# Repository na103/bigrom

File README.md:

# A590 Bigrom
Bigrom is an adapter that allows you to use a larger 256kbit ROM with the Commodore A590.<br>
It's useful for testing other firmwares that require more space and don't fit within the 128kbit limit imposed by the board's pinout.<br>
The ATF16V8C logic automatically asserts the A14 pin after reading the first 128kbit bank, allowing you to read the entire ROM content.
<br><br>

## Bill of materials
| Qt. |    Description     |             Designator          |    Mouser Part     |             Note              |
|:---:|--------------------|---------------------------------|--------------------|-------------------------------|
|1    |EEPROM 256K         |U2                               |AT28HC256F-90SU     |   need programmer like TL866  |
|1    |EEPLD               |U1                               |ATF16V8CZ-15SU      |   need programmer like TL866  |
|2    |Header Strip        |J1                               |D01-9923246         |                               |

## Building notes
The EEPROM can be soldered onto the PCB but it must be programmed before soldering the GAL (SW1 and SW3 closed).<br>
Programming of the ATF16V8 must be done before soldering using the TL866 with a SOIC socket adapter.<br>
in working configuration SW2,SW3 are closed and SW1 open, like a image above<br>
if the A590 Hard disk metal holder touches the rom you can remove the plastic from the header strips so as to lower the profile just enough for it to close properly.

<br>
If you found this my work useful, please consider buying me a cup of coffee if you want:<br>

# License

This work is licensed under a Creative Commons Attribution 4.0 International License. See [https://creativecommons.org/licenses/by/4.0/](https://creativecommons.org/licenses/by/4.0/).

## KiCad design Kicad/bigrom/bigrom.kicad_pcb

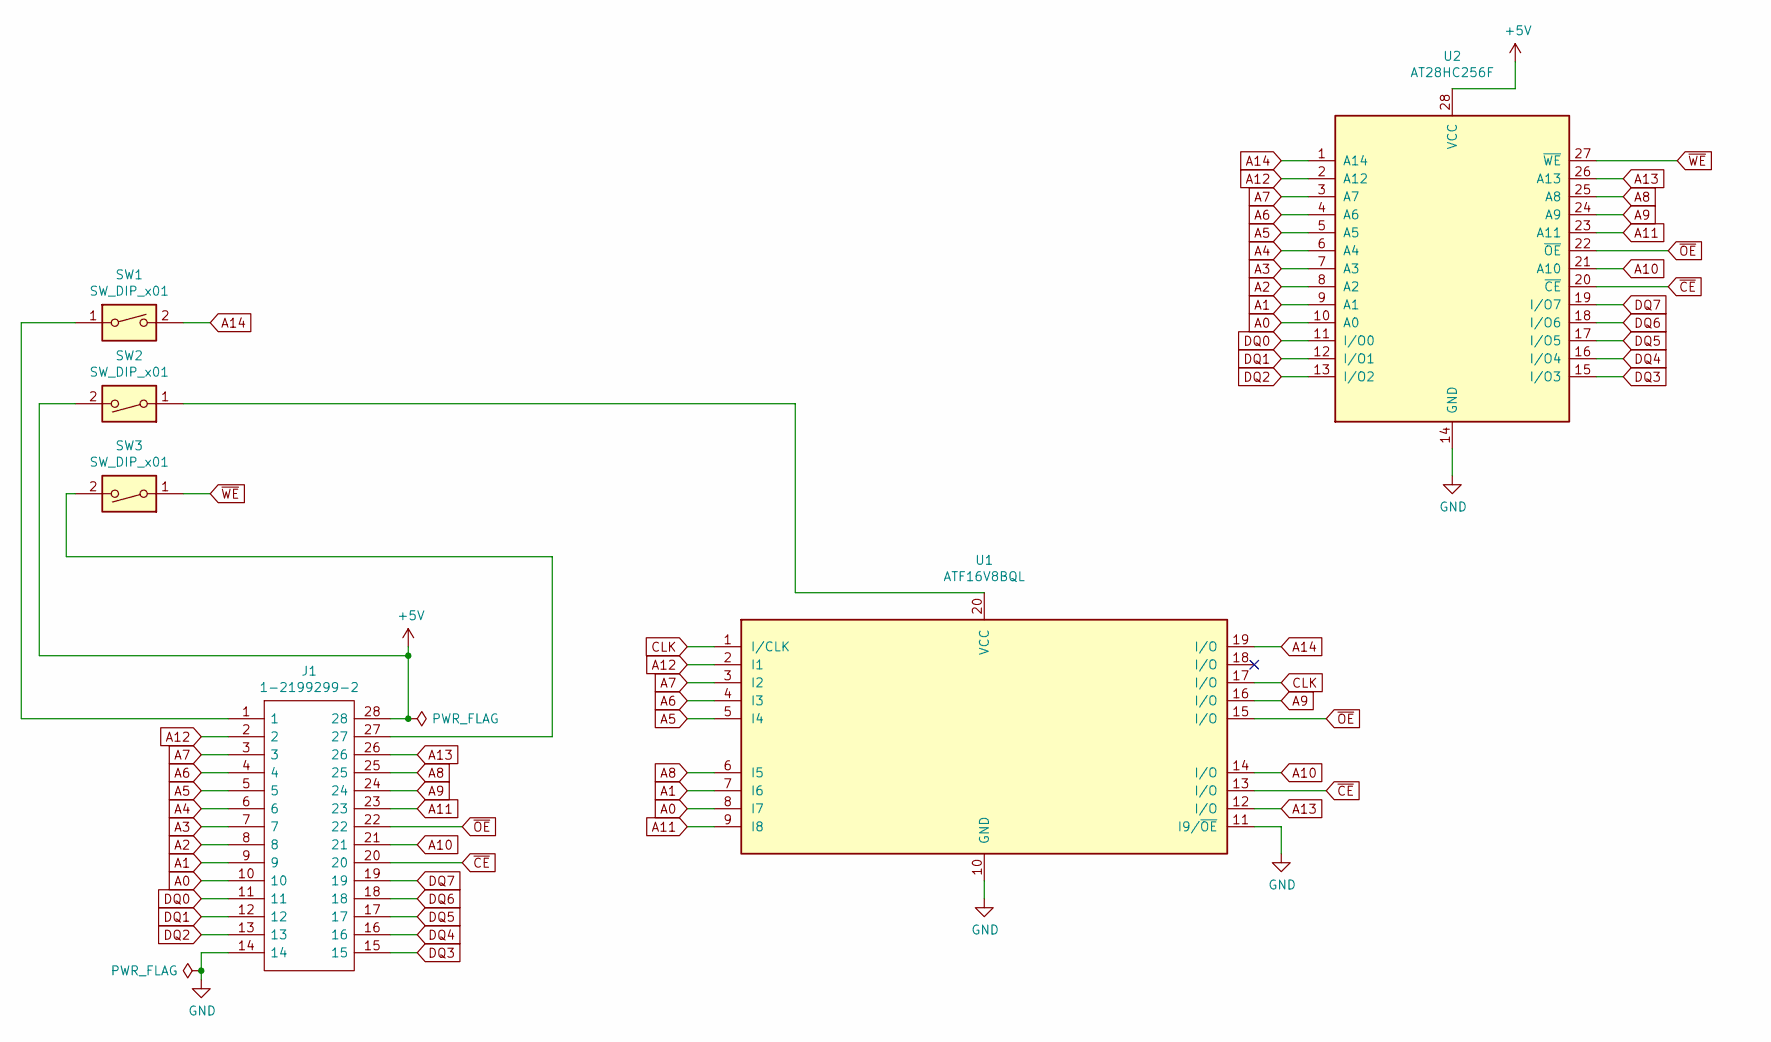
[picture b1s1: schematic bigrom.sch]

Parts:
J1: 1-2199299-2; DIPS1524W70P254L3556H530Q28N; Manufacturer_Part_Number 1-2199299-2; Mouser Part Number 571-1-2199299-2
SW1, SW2, SW3: SW_DIP_x01; SolderJumper-2_P1.3mm_Open_RoundedPad1.0x1.5mm
U1: ATF16V8BQL; SOIC-20W_7.5x12.8mm_P1.27mm
U2: AT28HC256F; SOIC-28W_7.5x17.9mm_P1.27mm

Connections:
+5V: J1.28, SW2.2, U2.28 (VCC)
A0: J1.10, U1.8 (I7), U2.10 (A0)
A1: J1.9, U1.7 (I6), U2.9 (A1)
A2: J1.8, U2.8 (A2)
A3: J1.7, U2.7 (A3)
A4: J1.6, U2.6 (A4)
A5: J1.5, U1.5 (I4), U2.5 (A5)
A6: J1.4, U1.4 (I3), U2.4 (A6)
A7: J1.3, U1.3 (I2), U2.3 (A7)
A8: J1.25, U1.6 (I5), U2.25 (A8)
A9: J1.24, U1.16 (I/O), U2.24 (A9)
A10: J1.21, U1.14 (I/O), U2.21 (A10)
A11: J1.23, U1.9 (I8), U2.23 (A11)
A12: J1.2, U1.2 (I1), U2.2 (A12)
A13: J1.26, U1.12 (I/O), U2.26 (A13)
A14: SW1.2, U1.19 (I/O), U2.1 (A14)
CLK: U1.1 (I/CLK), U1.17 (I/O)
DQ0: J1.11, U2.11 (I/O0)
DQ1: J1.12, U2.12 (I/O1)
DQ2: J1.13, U2.13 (I/O2)
DQ3: J1.15, U2.15 (I/O3)
DQ4: J1.16, U2.16 (I/O4)
DQ5: J1.17, U2.17 (I/O5)
DQ6: J1.18, U2.18 (I/O6)
DQ7: J1.19, U2.19 (I/O7)
GND: J1.14, U1.10 (GND), U1.11 (I9/~OE~), U2.14 (GND)
unnamed: J1.1, SW1.1
unnamed: J1.27, SW3.2
unnamed: SW2.1, U1.20 (VCC)
~CE~: J1.20, U1.13 (I/O), U2.20 (~CE~)
~OE~: J1.22, U1.15 (I/O), U2.22 (~OE~)
~WE~: SW3.1, U2.27 (~WE~)

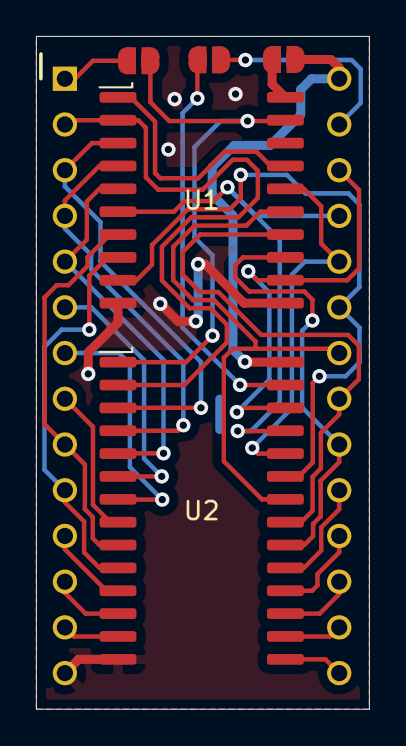
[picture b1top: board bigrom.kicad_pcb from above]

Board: 2 copper layers, 18.5 x 37.4 mm, 6 parts (0 on the bottom side), 32 nets.

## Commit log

2023-02-10 Update LICENSE
2023-02-10 Kicad project with gerber
2023-02-10 bigrom in a590
2023-02-10 Jed and Pld
